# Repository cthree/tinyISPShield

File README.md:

tinyISPShield
=============

** Important **
This project is in development and presently untested. Operation is
described as intended. This may not work at all, or worse, may damage your
parts or equipment. All risks are yours alone.

An Arduino UNO R3 Shield for programming ATtiny44/45/84/85 MCUs with Arduino 
sketches.

Arduino 1.0.5 comes with an example sketch named ArduinoISP. That sketch 
turns an Arduino Uno into a sketch programmer for other Atmel MCUs.

For more info on programming ATtiny series MCUs with Arduino sketches see 
[High-low tech blog](http://highlowtech.org/?p=1695)

Eagle CAD 6.5 Hobbist Edition used. Latest PCB available from 
[OSHPark](https://oshpark.com/shared_projects/PF0k6TW9)

Usage
-----

Choose the correct locations for the 3 MCU type selection jumper shunts.
They should all be aligned and all are necessary. Choose either:

- ATtiny44/84 (14-pin PDIP) or 
- ATtiny45/85 (8-pin PDIP).

Connect the shield to an Arduino UNO R3 and connect the Arduino to your
computer with a USB cable. The green READY LED should be blinking. If it
is not, check the connection and/or ensure the ArduinoISP sketch is loaded
on the base Arduino and that it is powered correctly.

1-Open the Arduino 1.0.5 IDE and load the sketch you want to upload to your
ATtiny part.
2-Choose the correct MCU from the IDE's Tools > Boards menu,
3-Choose 'Arduino as ISP' from the Tools > Programmer menu.
4-Insert the target ATtiny MCU in the ZIF socket. Verify the correct location
for pin 1 and the type selection jumper shunts.
5-Upload the sketch.

The yellow BUSY LED will illuminate when the part is being programmed.

The red ERROR LED will illuminate if there was an error uploading the 
last sketch.

Building
--------

I encourage you to build your own if you want to or find yourself using
ATtiny's for many projects. The ZIF if a 14 pin 3M "textool" 214-3339 part
available from Digikey. It's under $20. Not the cheapest. It does however
have 30um gold flash, 3x that of comparable parts in the Digikey catalog.
I personally hate tools that suck so I opted for the better part, I only
need one and I don't want to do this more than once. Rework it as you please.

The LEDs and limiting resistors are all optional. You can get away with
as few parts as the PCB, ZIF, and a 0.100" header strip. I populated
2 pins on each corner of the Arduino header layout for stability and ease
of alignment.

C1 is for an optional 0.1uF ceramic bypass cap. I don't find it necessary.

Development
-----------

If you wish to develop this project further please fork it on 
[github](https://github.com/cthree/tinyISPShield).

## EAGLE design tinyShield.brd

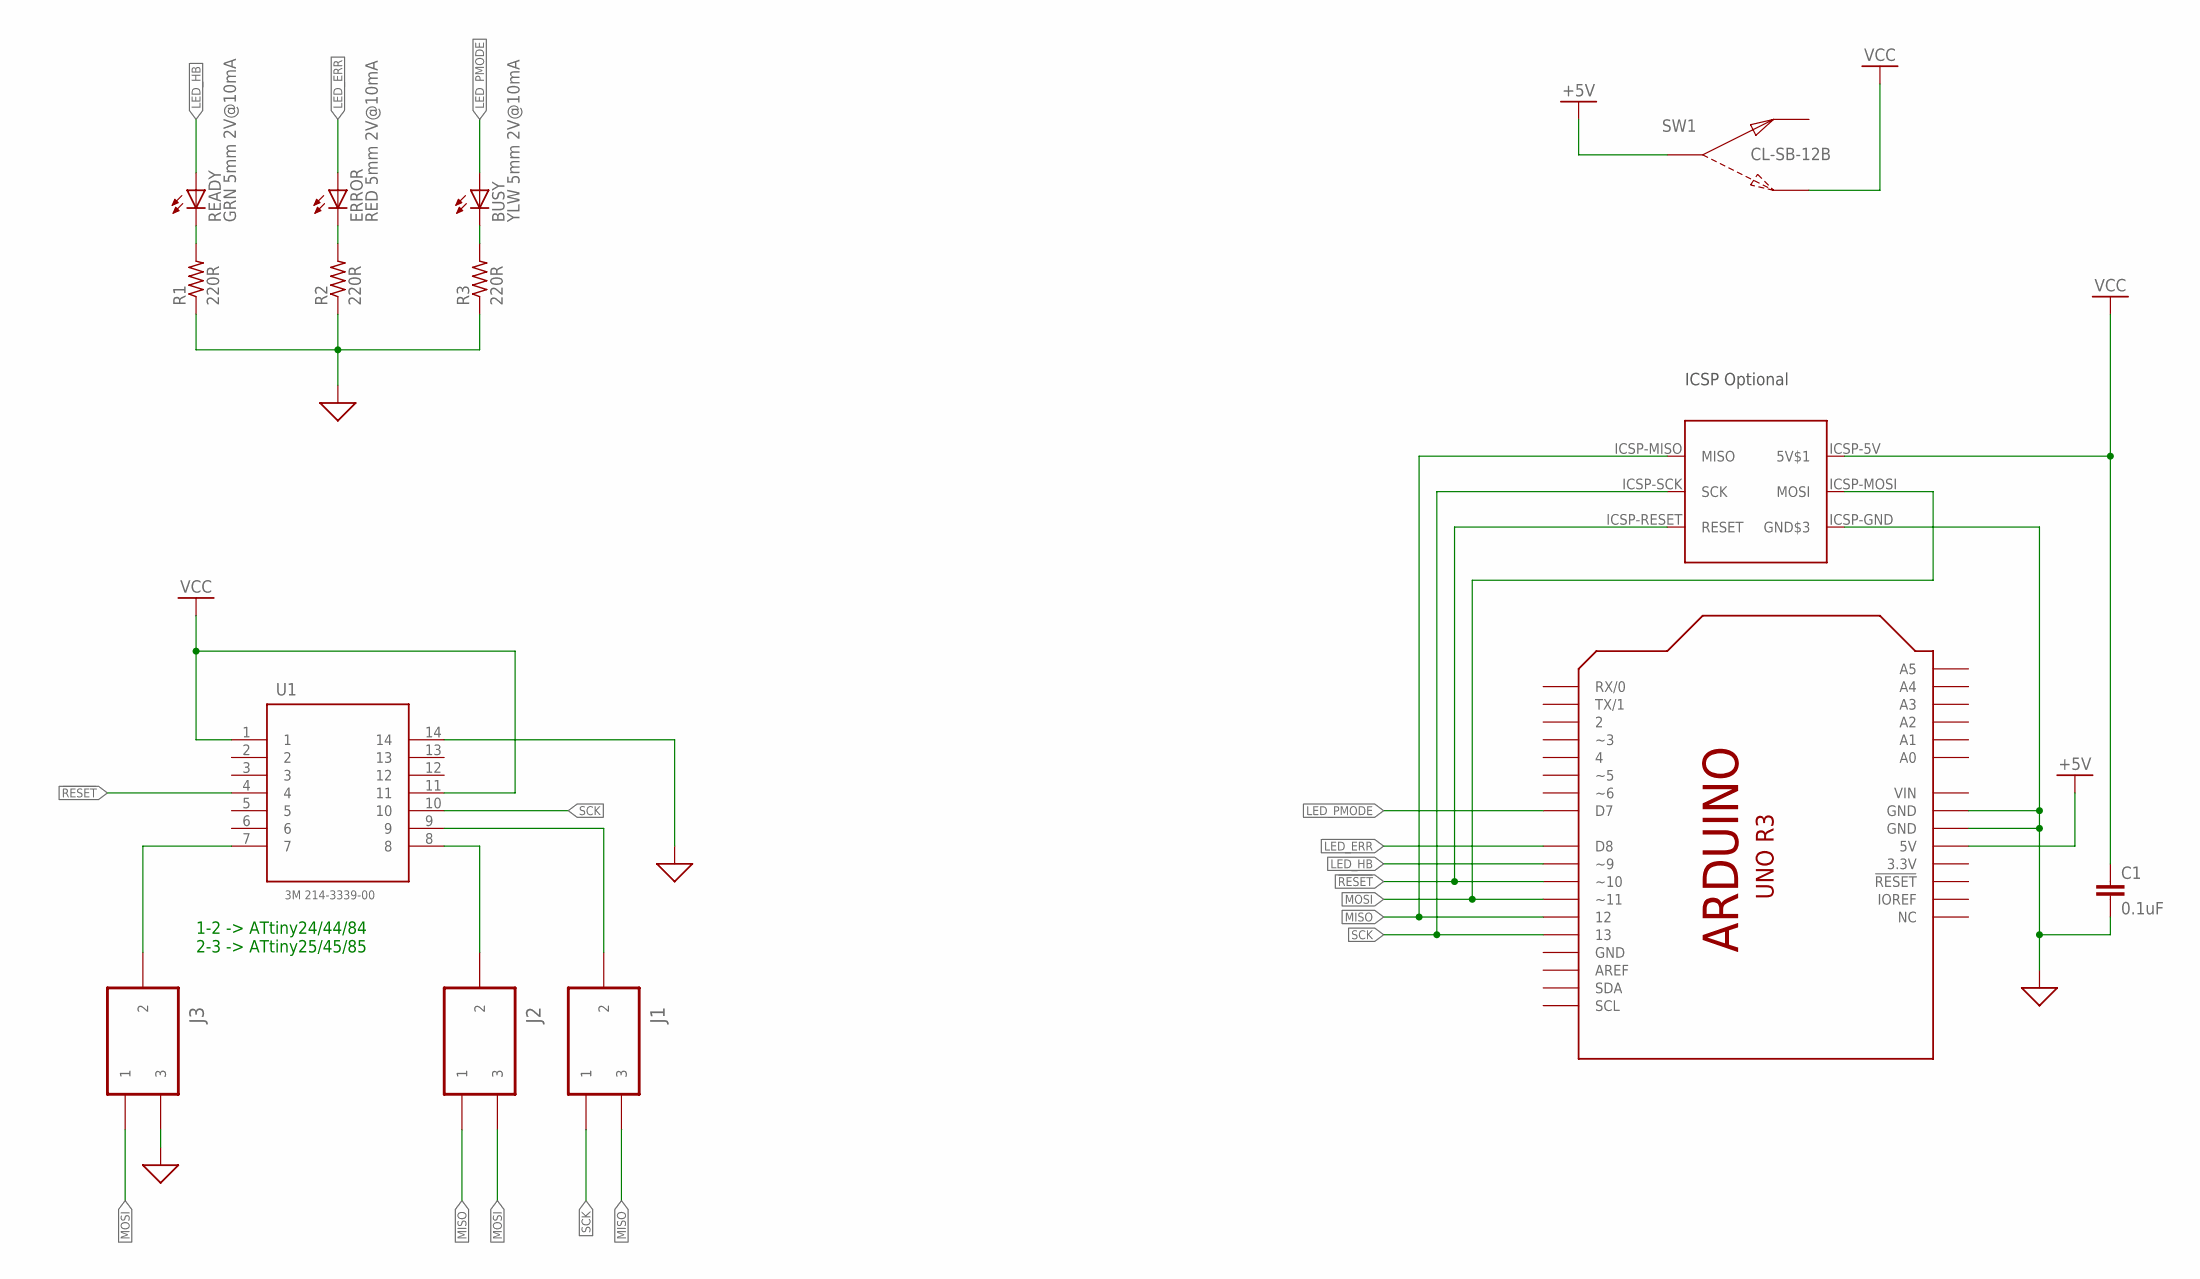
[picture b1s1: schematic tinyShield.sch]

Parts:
BUSY: YLW 5mm 2V@10mA; LED5MM
C1: 0.1uF; CAP-PTH-SMALL
ERROR: RED 5mm 2V@10mA; LED5MM
J1, J2, J3: TSW-103-07-L-SNO_SILK; 1X03_NO_SILK
R1, R2, R3: 220R; 0207/10
READY: GRN 5mm 2V@10mA; LED5MM
SW1: CL-SB-12B
U1: 3M 214-3339-00; 3M_214_3339
U$8: ARDUINO_R3_SHIELD; ARDUINO_SHIELD

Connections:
3.3V: U$8.3.3V
!RESET: U1.4, U$8.10 (~10), U$8.ICSP-RESET (RESET)
+5V: SW1.C (2), U$8.5V
GND: C1.2, J3.3, R1.1, R2.1, R3.1, U1.14, U$8.GND, U$8.GND$2 (GND), U$8.GND$3 (GND), U$8.ICSP-GND (GND$3)
LED_ERR: ERROR.A, U$8.8 (D8)
LED_HB: READY.A, U$8.9 (~9)
LED_PMODE: BUSY.A, U$8.7 (D7)
MISO: J1.3, J2.1, U$8.12, U$8.ICSP-MISO (MISO)
MOSI: J2.3, J3.1, U$8.11 (~11), U$8.ICSP-MOSI (MOSI)
unnamed: R1.2, READY.K (C)
unnamed: ERROR.K (C), R2.2
unnamed: BUSY.K (C), R3.2
unnamed: J3.2, U1.7
unnamed: J2.2, U1.8
unnamed: J1.2, U1.9
SCK: J1.1, U1.10, U$8.13, U$8.ICSP-SCK (SCK)
VCC: C1.1, SW1.3, U1.1, U1.11, U$8.ICSP-5V (5V$1)
VIN: U$8.VIN

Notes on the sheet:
1-2 -> ATtiny24/44/84 2-3 -> ATtiny25/45/85
ICSP Optional

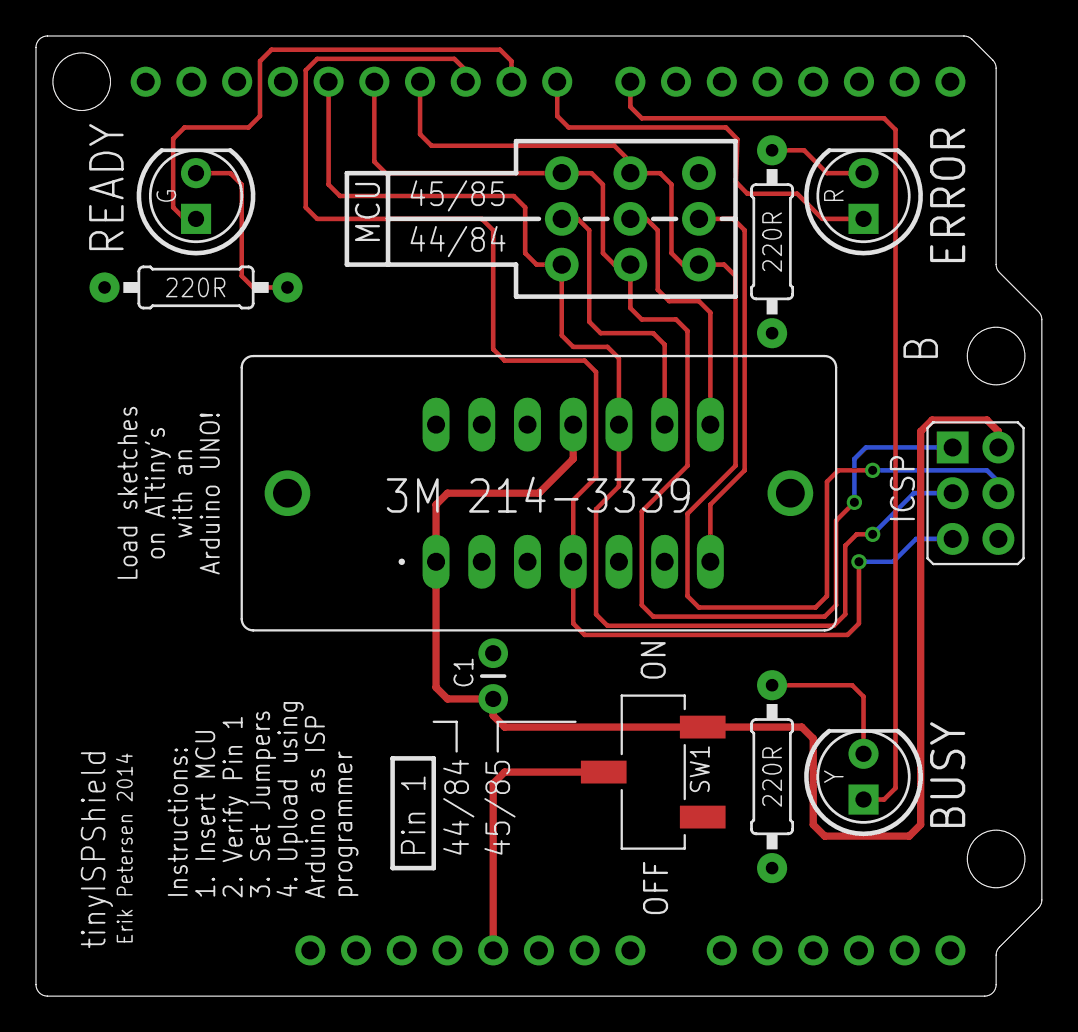
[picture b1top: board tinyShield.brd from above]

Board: 2 copper layers, 55.9 x 53.3 mm, 13 parts (0 on the bottom side), 16 nets.

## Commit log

2014-07-31 Add existing, update README
2014-08-01 Added PCB Images, updated README
2014-08-01 Rotate PCB images
2014-08-04 Added SW1 to switch 5V power from host Arduino; Update hardware rev to B

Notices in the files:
parts and their libraries:
SparkFun-Capacitors: Licensing: CC v3.0 Share-Alike You are welcome to use this library for commercial purposes.
